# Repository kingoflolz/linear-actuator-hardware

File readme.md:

# Linear Actuator Hardware

A fully integrated PCB linear actuator, with the motor driver, encoder and motor all on a single PCB. All designs are
open source:

- [Firmware and host software](https://github.com/kingoflolz/linear-actuator-firmware)
- [Blog post with commentary](https://benwang.dev/2022/08/09/PCB-Linear-Actuator.html)

Files in this repository are licensed under the Apache-2.0 license

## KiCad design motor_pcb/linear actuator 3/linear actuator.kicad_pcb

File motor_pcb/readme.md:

# PCB schematics and layouts

## Linear actuator

First version of the fully integrated linear actuator.

### Errata

- a few analog pins are not connected to analog inputs...
- encoder is not lined up with quadrature tracks (quadrature phase is not 90 degrees)

## Linear actuator 2

Second version, manufactured with 2 oz of copper.

### Errata

- there is a mistake with the motor windings, with the windings being abcABC instead of aBcAbC
- BOM forgot a part (diode for buck + misc power)
- Footprint for photodiodes are not ideal
- Encoder is not lined up with quadrature tracks (quadrature phase is not 90 degrees)

Otherwise, works fine!

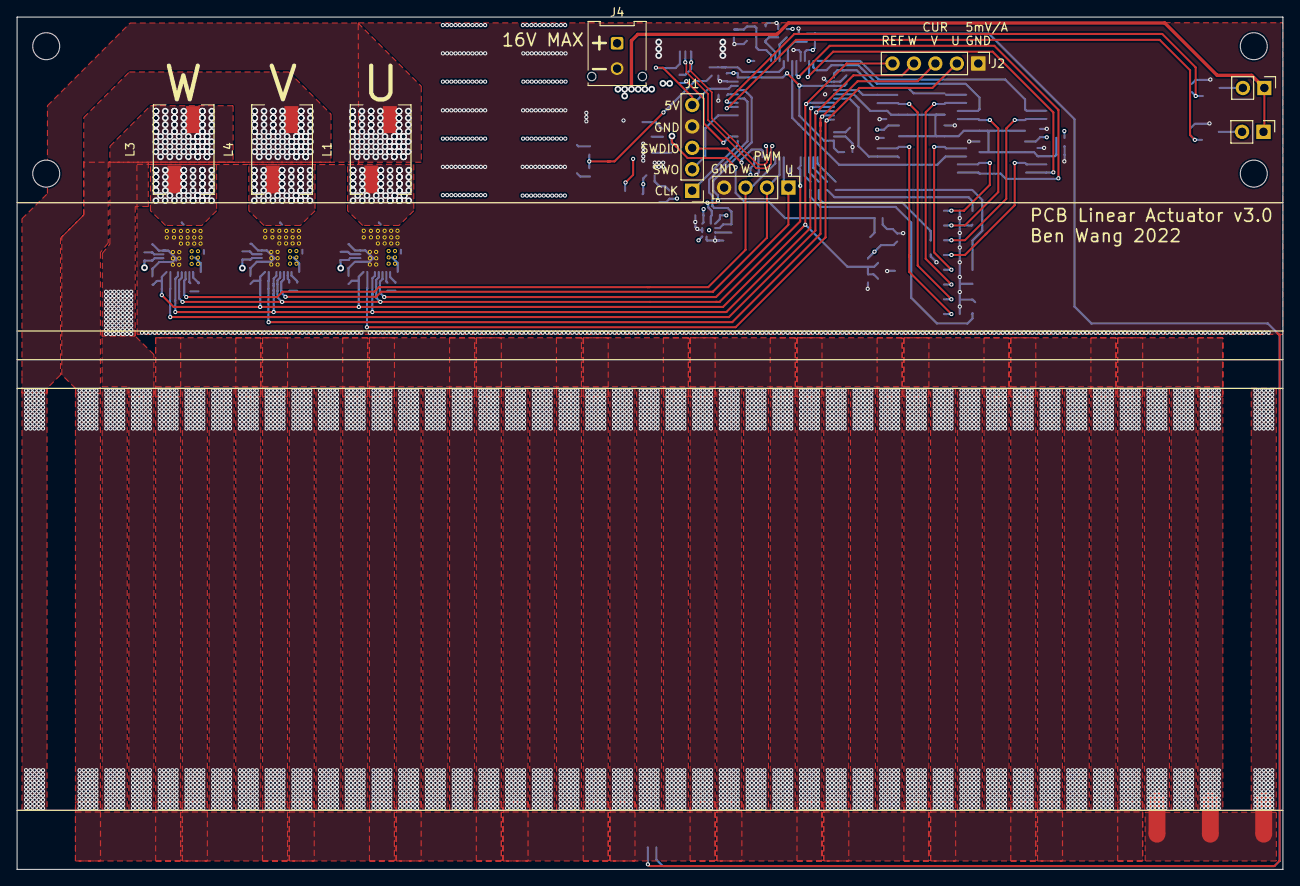
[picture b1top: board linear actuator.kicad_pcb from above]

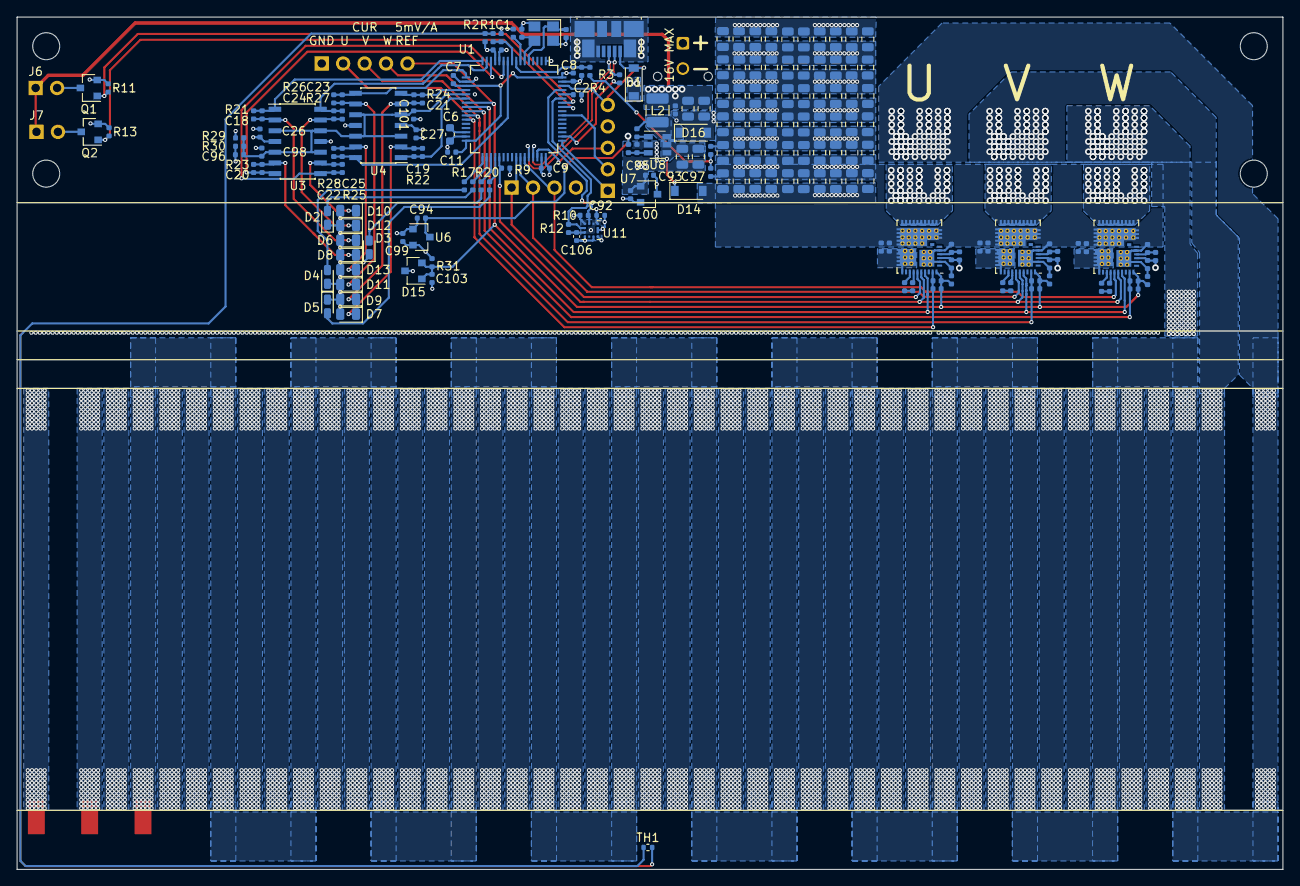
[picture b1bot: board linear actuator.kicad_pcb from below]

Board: 4 copper layers, 150.0 x 101.0 mm, 204 parts (188 on the bottom side), 84 nets.

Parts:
C1, C7, C8, C9, C11, C12, C13, C14, C17, C26, C27, C94, C95, C96, C98, C99, C100, C101, C103, C107, C108, C109, C112, C115, C116, C117, C120: 1uF; C_0402_1005Metric
C2, C102: 10nF; C_0402_1005Metric
C3, C4: 12pF; C_0402_1005Metric
C5: 1uF; R_0402_1005Metric
C6: 4.7uF; C_0603_1608Metric
C10, C105, C113: 22pF; C_0402_1005Metric
C15, C110, C118: 220nF; C_0402_1005Metric
C16, C92, C104, C106, C111, C119: 0.1uF; C_0402_1005Metric
C18, C19, C20, C21, C22, C23, C24, C25: 6pF; C_0402_1005Metric
C28, C29, C30, C31, C32, C33, C34, C35, C37, C38, C39, C40, C41, C43, C44, C45, C46, C47, C48, C49, C50, C51, C52, C53, C54, C55, C56, C57, C58, C59, C60, C61, C62, C63, C64, C65, C66, C67, C68, C69, C70, C71, C72, C73, C74, C75, C76, C77, C78, C79, C80, C81, C82, C83, C84, C85, C86, C87, C88, C89, C93, C97: 4.7uF; C_0805_2012Metric
C36, C42: 22uF; C_0805_2012Metric
D1, D14, D16: D; D_SOD-123
D2, D3, D4, D5: LED; D_0603_1608Metric_Castellated
D6, D7, D8, D9, D10, D11, D12, D13: D_Photo; D_0805_2012Metric
D15: TL432DBZ; SOT-23
J1, J2: Conn_01x05_Male; PinHeader_1x05_P2.54mm_Vertical
J3: USB_B_Micro; USB_Micro-B_Molex_47346-0001
J4: Conn_01x02_Male; Molex_Micro-Fit_3.0_43045-0212_2x01_P3.00mm_Vertical
J5: Conn_01x04_Male; PinHeader_1x04_P2.54mm_Vertical
J6, J7: Conn_01x02_Male; PinHeader_1x02_P2.54mm_Vertical
L1, L3, L4: L; L_10x7_H10
L2: 10uH; L_1210_3225Metric
MH1, MH2, MH3, MH4: MountingHole; MountingHole_3.2mm_M3
NT1, NT2, NT3: Net-Tie_2; NetTie-2_SMD_Pad2.0mm
Q1, Q2: Q_NMOS_GSD; SOT-23
R1, R2, R5, R9: 10K; R_0402_1005Metric
R3: 1K5; R_0402_1005Metric
R4, R6, R7, R8, R11, R13, R14, R30, R35, R39: 1K; R_0402_1005Metric
R10, R12: 2.2K; R_0402_1005Metric
R15, R16, R36, R37, R40, R41: 2R; R_0402_1005Metric
R17, R18, R19, R20: 300R; R_0402_1005Metric
R21, R22, R23, R24, R25, R26, R27, R28: 220K; R_0402_1005Metric
R29: 4K7; R_0402_1005Metric
R31: 220R; R_0402_1005Metric
R32: 68K; R_0402_1005Metric
R33: 13K; R_0402_1005Metric
TH1: 10K; R_0402_1005Metric
U1: STM32F412RETx; LQFP-64_10x10mm_P0.5mm
U2, U9, U10: FDMF3170; QFN-40_5x6_Pitch0.45mm
U3, U4: OPA4340UA; SOIC-14_3.9x8.7mm_P1.27mm
U6, U7: APE8865N-33-HF-3; SOT-23
U8: LMR16006YQ; SOT-23-6
U11: KXTJ3-1057; Kionix_LGA-12_2x2mm_P0.5mm_LayoutBorder2x4y
Y1: Crystal_GND24; Crystal_SMD_3225-4Pin_3.2x2.5mm

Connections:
+1V2: C10.2, C12.1, C103.1, C105.2, C107.1, C113.2, C115.1, D15.1 (REF), D15.2 (K), J2.5, R14.2, R31.2, R35.2, R39.2, U1.23 (PA7), U2.39 (REFIN), U9.39 (REFIN), U10.39 (REFIN)
+3.3V: C7.1, C8.1, C9.1, C11.1, C92.1, C100.2, C106.1, R7.2, R10.1, R12.1, U1.1 (VBAT), U1.19 (VDD), U1.32 (VDD), U1.48 (VDD), U1.64 (VDD), U7.2 (VO), U11.1 (ADDR), U11.3 (IO_VDD), U11.7 (VDD), U11.10 (VDD), U11.11 (IO_VDD)
+3.3VA: C5.1, C26.1, C27.1, C99.2, R2.1, R29.1, R31.1, U1.13 (VDDA), U3.4 (V+), U4.4 (V+), U6.2 (VO)
+5V: C14.1, C36.1, C42.1, C94.1, C95.1, C104.1, C109.1, C117.1, D1.1 (K), J6.1, J7.1, L2.1, R15.1, R32.1, R36.1, R40.1, U2.3 (VCC), U6.3 (VI), U7.3 (VI), U9.3 (VCC), U10.3 (VCC)
/D_TEMP: U1.24 (PC4), U2.36 (TMON), U9.36 (TMON), U10.36 (TMON)
/FAN1: Q1.1 (G), R11.1, U1.58 (PB6)
/FAN2: Q2.1 (G), R13.1, U1.57 (PB5)
/I_U: C10.1, J2.2, R14.1, U1.27 (PB1), U2.38 (IMON)
/I_V: C113.1, J2.3, R39.1, U1.26 (PB0), U10.38 (IMON)
/I_W: C105.1, J2.4, R35.1, U1.25 (PC5), U9.38 (IMON)
/L1: R17.1, U1.34 (PB13)
/L2: R18.1, U1.33 (PB12)
/L3: R19.1, U1.35 (PB14)
/L4: R20.1, U1.36 (PB15)
/M_TEMP: C1.1, R1.2, U1.9 (PC1)
/O1: C19.1, R22.1, U1.22 (PA6), U4.1
/O2: C21.1, R24.1, U1.20 (PA4), U4.7
/O3: C23.1, R26.1, U1.17 (PA3), U4.8
/O4: C25.1, R28.1, U1.10 (PC2), U4.14
/O5: C18.1, R21.1, U1.16 (PA2), U3.1
/O6: C20.1, R23.1, U1.14 (PA0), U3.7
/O7: C22.1, R25.1, U1.11 (PC3), U3.8
/O8: C24.1, R27.1, U1.15 (PA1), U3.14
/PWM_EN: R9.2, U1.37 (PC6), U2.35 (EN), U9.35 (EN), U10.35 (EN)
/PWM_U: J5.1, U1.41 (PA8), U2.34 (PWM)
/PWM_V: J5.2, U1.42 (PA9), U10.34 (PWM)
/PWM_W: J5.3, U1.43 (PA10), U9.34 (PWM)
/SCL: R10.2, U1.61 (PB8), U11.12 (SCL)
/SDA: R12.2, U1.59 (PB7), U11.2 (SDA)
/STAR: NT1.2, NT2.2, NT3.2
/SWCLK: J1.1, U1.49 (PA14)
/SWDIO: J1.3, U1.46 (PA13)
/SWO: J1.2, U1.55 (PB3)
/U/MOTOR: L1.2, NT3.1
/USB_N: J3.2 (D-), U1.44 (PA11)
/USB_P: J3.3 (D+), R3.2, U1.45 (PA12)
/USB_PULL: R3.1, U1.50 (PA15)
/USB_S: D1.2 (A), J1.5, J3.1 (VBUS), U1.62 (PB9)
/V/MOTOR: L4.2, NT1.1
/VBUS_S: C2.1, R4.2, U1.8 (PC0)
/W/MOTOR: L3.2, NT2.1
/power/VBUS_D: C93.2, C97.2, D14.1 (K), U8.4 (~SHDN), U8.5 (VIN)
GND: C1.2, C2.2, C3.2, C4.2, C5.2, C6.2, C7.2, C8.2, C9.2, C11.2, C12.2, C13.2, C14.2, C16.1, C17.1, C26.2, C27.2, C28.1, C29.1, C30.1, C31.1, C32.1, C33.1, C34.1, C35.1, C36.2, C37.1, C38.1, C39.1, C40.1, C41.1, C42.2, C43.1, C44.1, C45.1, C46.1, C47.1, C48.1, C49.1, C50.1, C51.1, C52.1, C53.1, C54.1, C55.1, C56.1, C57.1, C58.1, C59.1, C60.1, C61.1, C62.1, C63.1, C64.1, C65.1, C66.1, C67.1, C68.1, C69.1, C70.1, C71.1, C72.1, C73.1, C74.1, C75.1, C76.1, C77.1, C78.1, C79.1, C80.1, C81.1, C82.1, C83.1, C84.1, C85.1, C86.1, C87.1, C88.1, C89.1, C92.2, C93.1, C94.2, C95.2, C96.1, C97.1, C98.1, C99.1, C100.1, C101.1, C103.2, C104.2, C106.2, C107.2, C108.2, C109.2, C111.1, C112.1, C115.2, C116.2, C117.2, C119.1, C120.1, D2.1 (K), D3.1 (K), D4.1 (K), D5.1 (K), D6.2 (A), D7.2 (A), D8.2 (A), D9.2 (A), D10.2 (A), D11.2 (A), D12.2 (A), D13.2 (A), D15.3 (A), D16.2 (A), J1.4, J2.1, J3.5 (GND), J3.6 (Shield), J4.2, J5.4, Q1.2 (S), Q2.2 (S), R6.2, R8.2, R9.1, R11.2, R13.2, R30.2, R33.2, TH1.2, U1.12 (VSSA), U1.18 (VSS), U1.31 (VSS), U1.47 (VSS), U1.63 (VSS), U2.2 (AGND), U2.5 (PGND), U2.7 (PGND), U2.40 (PGND), U3.11 (V-), U4.11 (V-), U6.1 (GND), U7.1 (GND), U8.2 (GND), U9.2 (AGND), U9.5 (PGND), U9.7 (PGND), U9.40 (PGND), U10.2 (AGND), U10.5 (PGND), U10.7 (PGND), U10.40 (PGND), U11.4 (RES), U11.6 (GND), U11.8 (GND), U11.9 (GND), Y1.2, Y1.4
unnamed: C3.1, U1.5 (PH0), Y1.1
unnamed: C4.1, U1.6 (PH1), Y1.3
unnamed: C6.1, U1.30 (VCAP_1)
unnamed: C13.1, R15.2, U2.4 (PVCC)
unnamed: C15.1, R16.1
unnamed: C15.2, U2.32 (PHASE)
unnamed: C18.2, D6.1 (K), R21.2, U3.2 (-)
unnamed: C19.2, D7.1 (K), R22.2, U4.2 (-)
unnamed: C20.2, D8.1 (K), R23.2, U3.6 (-)
unnamed: C21.2, D9.1 (K), R24.2, U4.6 (-)
unnamed: C22.2, D10.1 (K), R25.2, U3.9 (-)
unnamed: C23.2, D11.1 (K), R26.2, U4.9 (-)
unnamed: C24.2, D12.1 (K), R27.2, U3.13 (-)
unnamed: C25.2, D13.1 (K), R28.2, U4.13 (-)
unnamed: C102.1, U8.1 (CB)
unnamed: C102.2, D16.1 (K), L2.2, U8.6 (SW)
unnamed: C108.1, R36.2, U9.4 (PVCC)
unnamed: C110.1, R37.1
unnamed: C110.2, U9.32 (PHASE)
unnamed: C116.1, R40.2, U10.4 (PVCC)
unnamed: C118.1, R41.1
unnamed: C118.2, U10.32 (PHASE)
unnamed: D2.2 (A), R17.2
unnamed: D3.2 (A), R19.2
unnamed: D4.2 (A), R18.2
unnamed: D5.2 (A), R20.2
unnamed: J6.2, Q1.3 (D)
unnamed: J7.2, Q2.3 (D)
unnamed: L1.1, U2.10 (SW)
unnamed: L3.1, U9.10 (SW)
unnamed: L4.1, U10.10 (SW)
unnamed: R1.1, R2.2, TH1.1
unnamed: R4.1, R5.2, R6.1
unnamed: R7.1, U1.7 (NRST)
unnamed: R8.1, U1.60 (BOOT0)
unnamed: R16.2, U2.33 (BOOT)
unnamed: R32.2, R33.1, U8.3 (FB)
unnamed: R37.2, U9.33 (BOOT)
unnamed: R41.2, U10.33 (BOOT)
VBUS: C16.2, C17.2, C28.2, C29.2, C30.2, C31.2, C32.2, C33.2, C34.2, C35.2, C37.2, C38.2, C39.2, C40.2, C41.2, C43.2, C44.2, C45.2, C46.2, C47.2, C48.2, C49.2, C50.2, C51.2, C52.2, C53.2, C54.2, C55.2, C56.2, C57.2, C58.2, C59.2, C60.2, C61.2, C62.2, C63.2, C64.2, C65.2, C66.2, C67.2, C68.2, C69.2, C70.2, C71.2, C72.2, C73.2, C74.2, C75.2, C76.2, C77.2, C78.2, C79.2, C80.2, C81.2, C82.2, C83.2, C84.2, C85.2, C86.2, C87.2, C88.2, C89.2, C111.2, C112.2, C119.2, C120.2, D14.2 (A), J4.1, R5.1, U2.25 (VIN), U2.30 (VIN), U9.25 (VIN), U9.30 (VIN), U10.25 (VIN), U10.30 (VIN)
V_BIAS: C96.2, C98.2, C101.2, R29.2, R30.1, U1.21 (PA5), U3.3 (+), U3.5 (+), U3.10 (+), U3.12 (+), U4.3 (+), U4.5 (+), U4.10 (+), U4.12 (+)

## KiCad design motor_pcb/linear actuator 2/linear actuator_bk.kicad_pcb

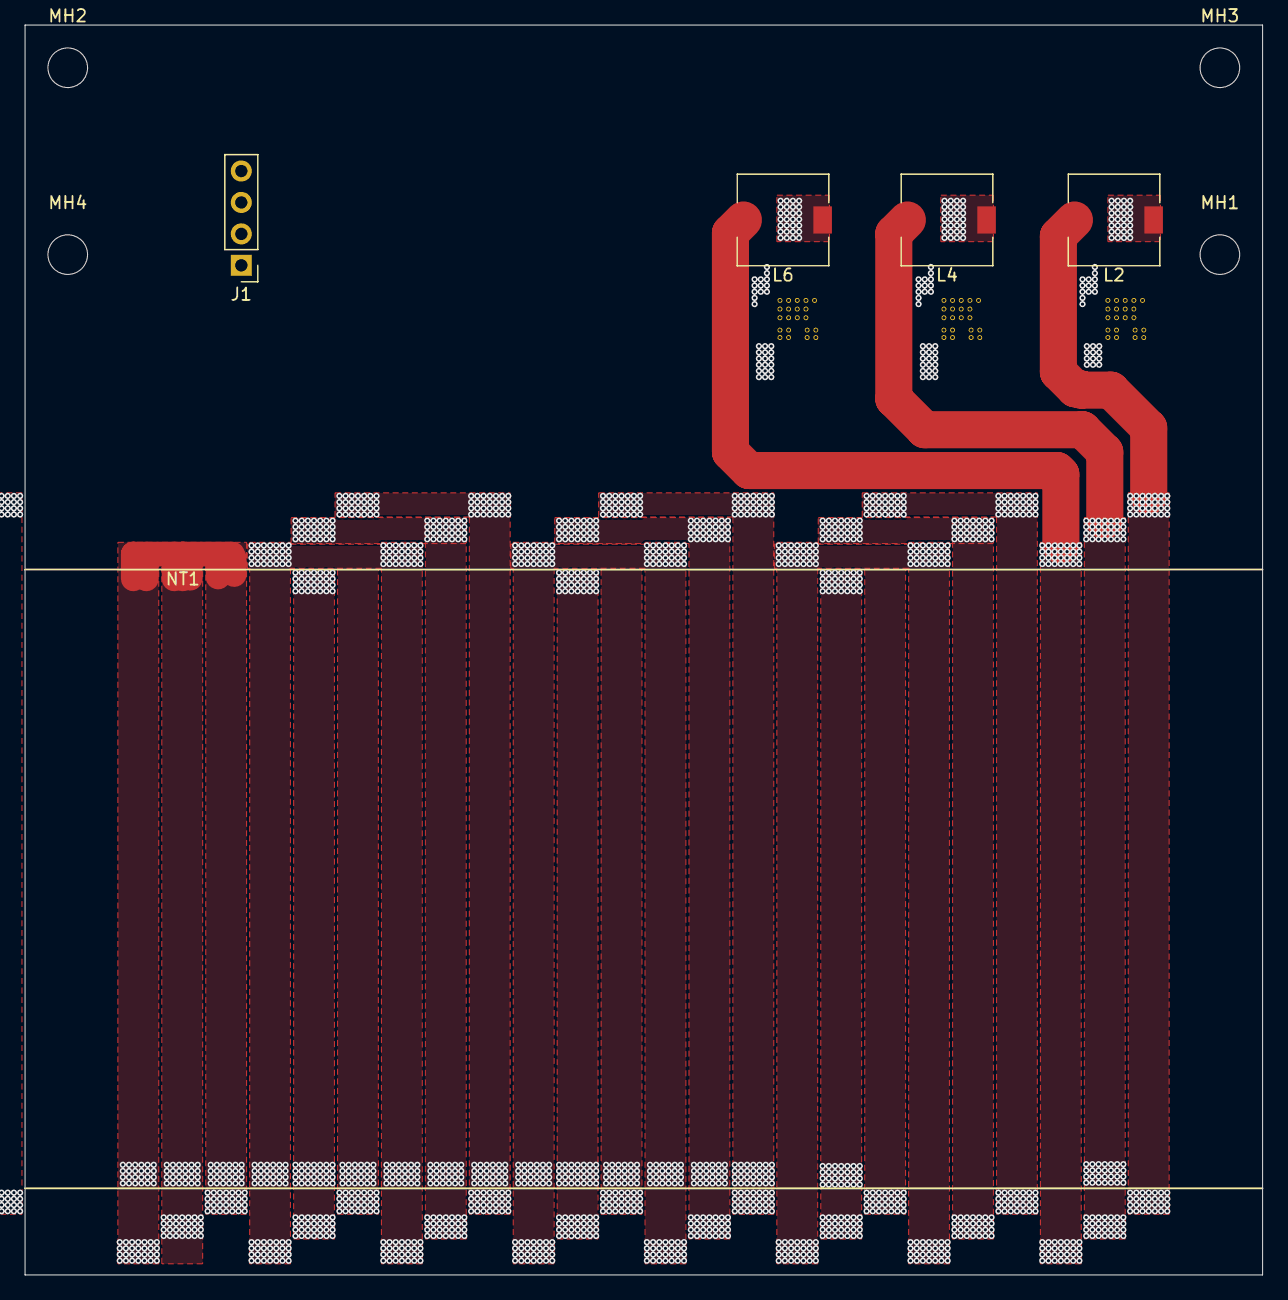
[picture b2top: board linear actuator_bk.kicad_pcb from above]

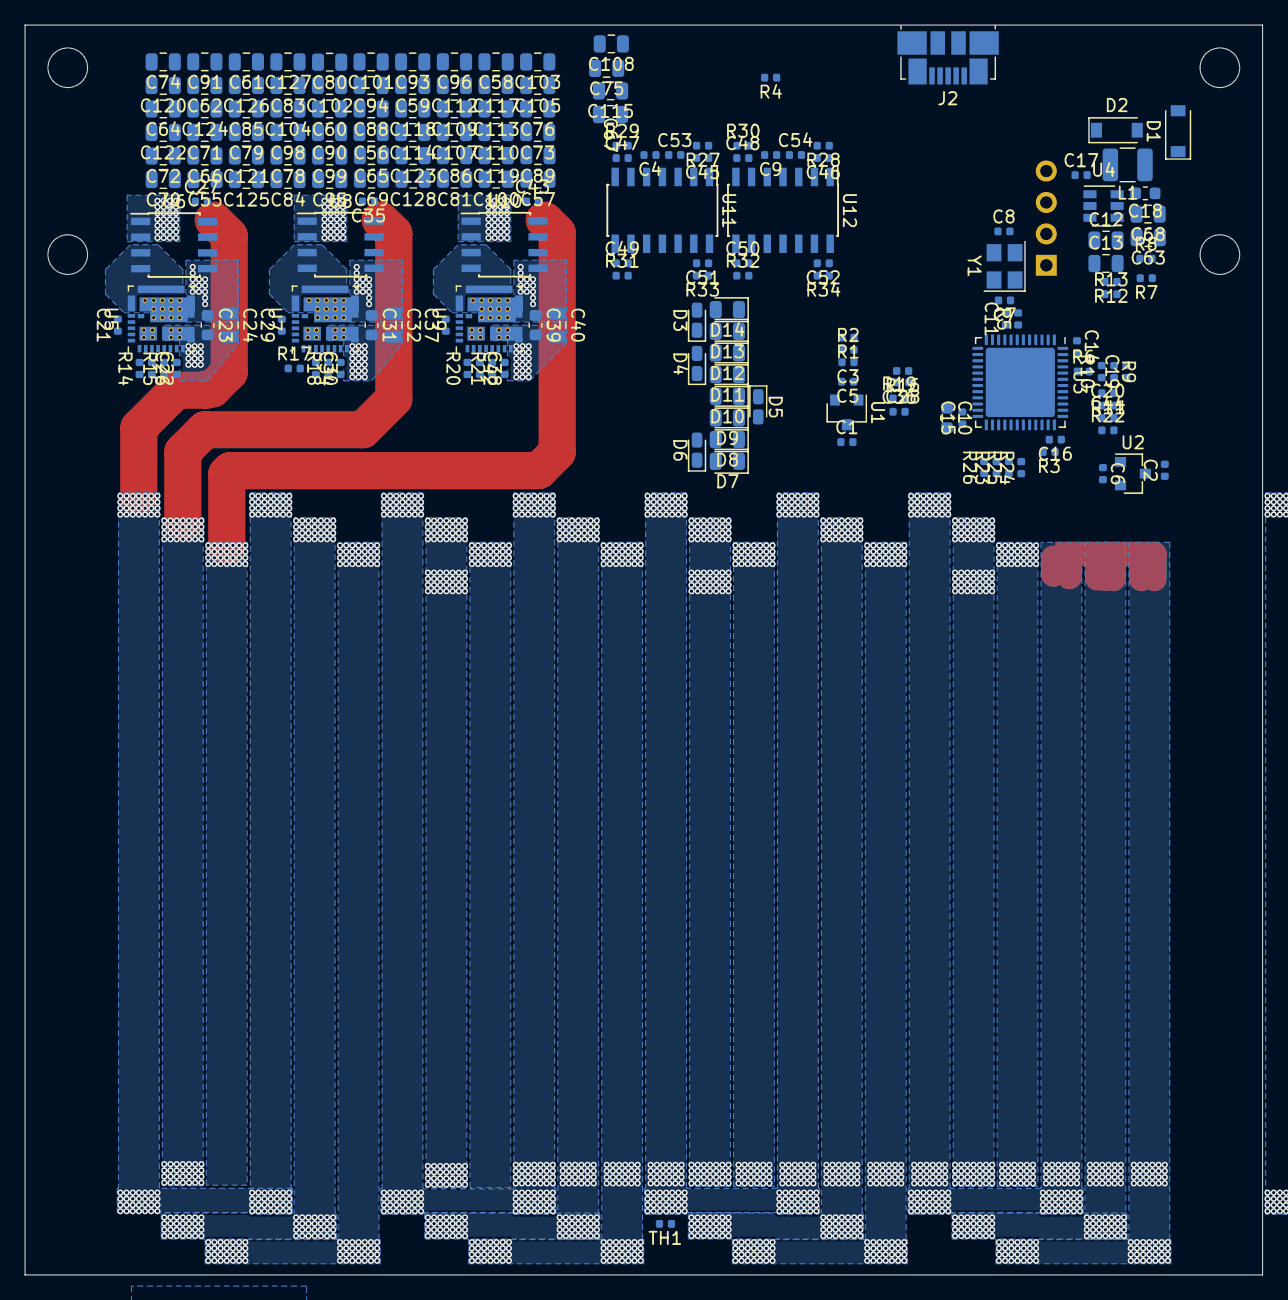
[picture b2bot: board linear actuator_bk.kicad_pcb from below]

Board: 4 copper layers, 100.0 x 101.0 mm, 190 parts (181 on the bottom side), 84 nets.

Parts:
C1, C2, C3, C4, C5, C6, C9, C14, C15, C16, C19, C21, C22, C27, C29, C30, C35, C37, C38, C43, C53, C54: 1uF; C_0402_1005Metric
C7, C8: 12pF; C_0402_1005Metric
C10: 4.7uF; C_0603_1608Metric
C11: 1uF; R_0402_1005Metric
C12, C13, C24, C32, C40, C55, C56, C57, C58, C59, C60, C61, C62, C64, C65, C66, C67, C69, C70, C71, C72, C73, C74, C75, C76, C78, C79, C80, C81, C83, C84, C85, C86, C88, C89, C90, C91, C93, C94, C95, C96, C98, C99, C100, C101, C102, C103, C104, C105, C107, C108, C109, C110, C112, C113, C114, C115, C117, C118, C119, C120, C121, C122, C123, C124, C125, C126, C127, C128: 4.7uF; C_0805_2012Metric
C17, C20, C28, C36, C44: 10nF; C_0402_1005Metric
C18, C23, C31, C39: 0.1uF; C_0603_1608Metric
C26, C34, C42: 100nF; C_0402_1005Metric
C45, C46, C47, C48, C49, C50, C51, C52: 6pF; C_0402_1005Metric
C63, C68: 22uF; C_0805_2012Metric
D1, D2: D; D_SOD-123
D3, D4, D5, D6: LED; D_0603_1608Metric_Castellated
D7, D8, D9, D10, D11, D12, D13, D14: D_Photo; D_0805_2012Metric
J1: Conn_01x04_Male; PinHeader_1x04_P2.54mm_Vertical
J2: USB_B_Micro; USB_Micro-B_Molex_47346-0001
L1: 10uH; L_1210_3225Metric
L2, L4, L6: L; L_7.3x7.3_H4.5
MH1, MH2, MH3, MH4: MountingHole; MountingHole_3.2mm_M3
NT1: Net-Tie_3_Tee; NetTie-3_SMD_Pad2.0mm
R1: 4K7; R_0402_1005Metric
R2, R5, R6, R11, R13: 1K; R_0402_1005Metric
R3: 1K5; R_0402_1005Metric
R4, R9, R10, R12, R16, R19, R22: 10K; R_0402_1005Metric
R7: 68K; R_0402_1005Metric
R8: 13K; R_0402_1005Metric
R14, R17, R20: 10R; R_0402_1005Metric
R15, R18, R21: 2R; R_0402_1005Metric
R23, R24, R25, R26: 150R; R_0402_1005Metric
R27, R28, R29, R30, R31, R32, R33, R34: 220K; R_0402_1005Metric
TH1: 10K; R_0402_1005Metric
U1, U2: APE8865N-33-HF-3; SOT-23
U3: STM32F411CEUx; QFN-48-1EP_7x7mm_P0.5mm_EP5.6x5.6mm
U4: LMR16006YQ; SOT-23-6
U5, U7, U9: NCP302155; PQFN-31_5x5_Pitch0.5mm
U6, U8, U10: ACS712xLCTR-20A; SOIC-8_3.9x4.9mm_P1.27mm
U11, U12: OPA4340UA; SOIC-14_3.9x8.7mm_P1.27mm
Y1: Crystal_GND24; Crystal_SMD_3225-4Pin_3.2x2.5mm

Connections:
+3.3VA: C5.2, C11.1, C27.2, C35.2, C43.2, C53.1, C54.1, R1.1, R10.1, U1.2, U3.9, U6.8, U8.8, U10.8, U11.4, U12.4
+3V3: C6.2, C14.1, C15.1, C16.1, R4.1, R5.2, U2.2, U3.1, U3.24, U3.36, U3.48
+5V: C1.1, C2.1, C18.1, C21.1, C29.1, C37.1, C63.1, C68.1, D1.1, J1.4, L1.1, R7.1, R14.1, R17.1, R20.1, U1.3, U2.3, U5.29, U7.29, U9.29
/Encoder/V_BIAS: U11.3, U11.5, U11.10, U11.12, U12.3, U12.5, U12.10, U12.12
/I_U: C28.1, R16.1, U3.19
/I_V: C36.1, R19.1, U3.20
/I_W: C44.1, R22.1, U3.39
/L1: R23.1, U3.45
/L2: R24.1, U3.46
/L3: R25.1, U3.28
/L4: R26.1, U3.27
/M_TEMP: C19.1, R9.2, U3.42
/O1: C46.1, R28.1, U3.14, U12.1
/O2: C48.1, R30.1, U3.15, U12.7
/O3: C50.1, R32.1, U3.16, U12.8
/O4: C52.1, R34.1, U3.17, U12.14
/O5: C45.1, R27.1, U3.13, U11.1
/O6: C47.1, R29.1, U3.10, U11.7
/O7: C49.1, R31.1, U3.11, U11.8
/O8: C51.1, R33.1, U3.12, U11.14
/PWM_EN: U3.40, U5.31, U7.31, U9.31
/PWM_U: U3.29, U5.1
/PWM_V: U3.30, U7.1
/PWM_W: U3.31, U9.1
/SWCLK: J1.1, U3.37
/SWDIO: J1.2, U3.34
/THWN: R4.2, U3.41, U5.30, U7.30, U9.30
/U/MOTOR: L2.2, NT1.1
/USB_N: J2.2, U3.32
/USB_P: J2.3, R3.2, U3.33
/USB_PULL: R3.1, U3.38
/USB_S: D1.2, J2.1, U3.26
/V/MOTOR: L4.2, NT1.2
/VBUS_S: C20.1, R11.2, U3.43
/V_BIAS: C3.2, C4.2, C9.2, R1.2, R2.1, U3.18
/W/MOTOR: L6.2, NT1.3
GND: C1.2, C2.2, C3.1, C4.1, C5.1, C6.1, C7.2, C8.2, C9.1, C10.2, C11.2, C12.1, C13.1, C14.2, C15.2, C16.2, C18.2, C19.2, C20.2, C21.2, C22.2, C23.1, C24.1, C27.1, C28.2, C29.2, C30.2, C31.1, C32.1, C35.1, C36.2, C37.2, C38.2, C39.1, C40.1, C43.1, C44.2, C53.2, C54.2, C55.1, C56.1, C57.1, C58.1, C59.1, C60.1, C61.1, C62.1, C63.2, C64.1, C65.1, C66.1, C67.1, C68.2, C69.1, C70.1, C71.1, C72.1, C73.1, C74.1, C75.1, C76.1, C78.1, C79.1, C80.1, C81.1, C83.1, C84.1, C85.1, C86.1, C88.1, C89.1, C90.1, C91.1, C93.1, C94.1, C95.1, C96.1, C98.1, C99.1, C100.1, C101.1, C102.1, C103.1, C104.1, C105.1, C107.1, C108.1, C109.1, C110.1, C112.1, C113.1, C114.1, C115.1, C117.1, C118.1, C119.1, C120.1, C121.1, C122.1, C123.1, C124.1, C125.1, C126.1, C127.1, C128.1, D2.2, D3.1, D4.1, D5.1, D6.1, D7.2, D8.2, D9.2, D10.2, D11.2, D12.2, D13.2, D14.2, J1.3, J2.5, J2.6, R2.2, R6.2, R8.2, R13.2, TH1.2, U1.1, U2.1, U3.8, U3.23, U3.35, U3.47, U3.49, U4.2, U5.4, U5.12, U5.28, U5.32, U6.5, U7.4, U7.12, U7.28, U7.32, U8.5, U9.4, U9.12, U9.28, U9.32, U10.5, U11.11, U12.11, Y1.2, Y1.4
unnamed: C7.1, U3.5, Y1.1
unnamed: C8.1, U3.6, Y1.3
unnamed: C10.1, U3.22
unnamed: C17.1, U4.1
unnamed: C17.2, D2.1, L1.2, U4.6
unnamed: C22.1, R14.2, U5.3
unnamed: C26.1, R15.1
unnamed: C26.2, U5.7
unnamed: C30.1, R17.2, U7.3
unnamed: C34.1, R18.1
unnamed: C34.2, U7.7
unnamed: C38.1, R20.2, U9.3
unnamed: C42.1, R21.1
unnamed: C42.2, U9.7
unnamed: C45.2, D7.1, R27.2, U11.2
unnamed: C46.2, D8.1, R28.2, U12.2
unnamed: C47.2, D9.1, R29.2, U11.6
unnamed: C48.2, D10.1, R30.2, U12.6
unnamed: C49.2, D11.1, R31.2, U11.9
unnamed: C50.2, D12.1, R32.2, U12.9
unnamed: C51.2, D13.1, R33.2, U11.13
unnamed: C52.2, D14.1, R34.2, U12.13
unnamed: D3.2, R23.2
unnamed: D4.2, R24.2
unnamed: D5.2, R25.2
unnamed: D6.2, R26.2
unnamed: L2.1, U6.1, U6.2
unnamed: L4.1, U8.1, U8.2
unnamed: L6.1, U10.1, U10.2
unnamed: R5.1, U3.7
unnamed: R6.1, U3.44
unnamed: R7.2, R8.1, U4.3
unnamed: R9.1, R10.2, TH1.1
unnamed: R11.1, R12.2, R13.1
unnamed: R15.2, U5.5
unnamed: R16.2, U6.7
unnamed: R18.2, U7.5
unnamed: R19.2, U8.7
unnamed: R21.2, U9.5
unnamed: R22.2, U10.7
unnamed: U5.16, U6.3, U6.4
unnamed: U5.27, U5.33
unnamed: U7.16, U8.3, U8.4
unnamed: U7.27, U7.33
unnamed: U9.27, U9.33
unnamed: U9.16, U10.3, U10.4
VBUS: C12.2, C13.2, C23.2, C24.2, C31.2, C32.2, C39.2, C40.2, C55.2, C56.2, C57.2, C58.2, C59.2, C60.2, C61.2, C62.2, C64.2, C65.2, C66.2, C67.2, C69.2, C70.2, C71.2, C72.2, C73.2, C74.2, C75.2, C76.2, C78.2, C79.2, C80.2, C81.2, C83.2, C84.2, C85.2, C86.2, C88.2, C89.2, C90.2, C91.2, C93.2, C94.2, C95.2, C96.2, C98.2, C99.2, C100.2, C101.2, C102.2, C103.2, C104.2, C105.2, C107.2, C108.2, C109.2, C110.2, C112.2, C113.2, C114.2, C115.2, C117.2, C118.2, C119.2, C120.2, C121.2, C122.2, C123.2, C124.2, C125.2, C126.2, C127.2, C128.2, R12.1, U4.4, U4.5, U5.8, U7.8, U9.8

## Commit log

2022-08-09 readme
2022-08-09 license
2022-08-09 blog post url
2022-08-25 v3 hardware
